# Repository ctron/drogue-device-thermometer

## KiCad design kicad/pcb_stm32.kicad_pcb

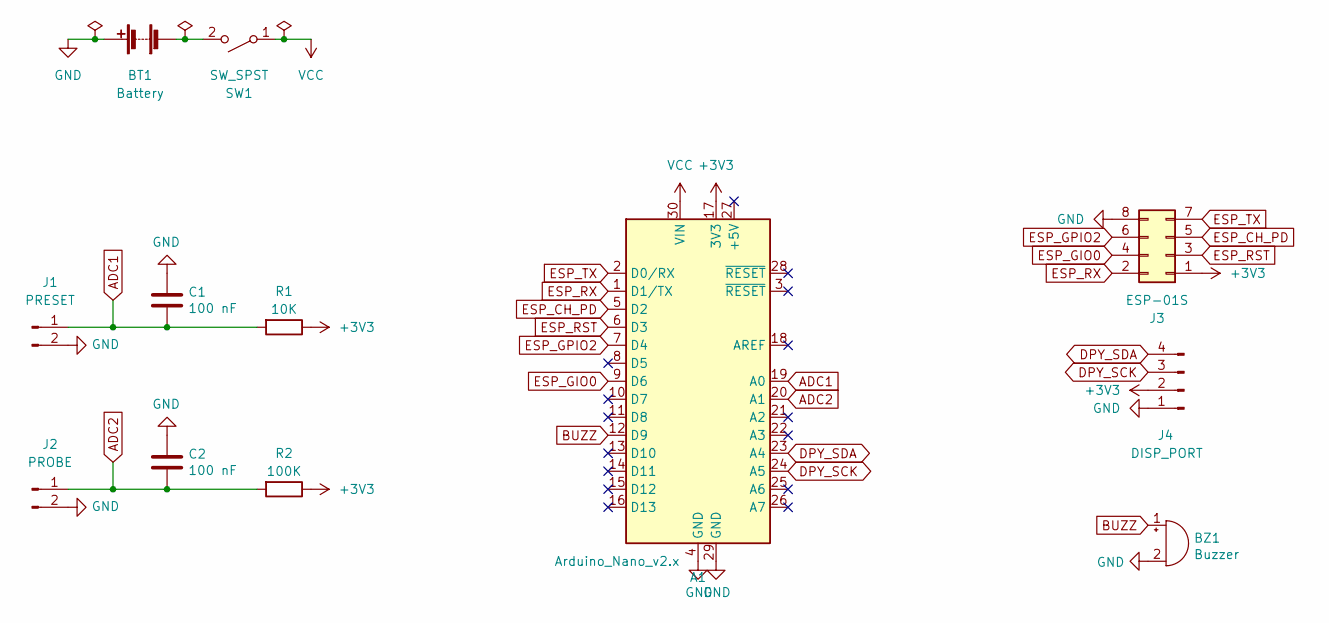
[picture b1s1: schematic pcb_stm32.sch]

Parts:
A1: Arduino_Nano_v2.x; Arduino_Nano
BT1: Battery; JST_PH_B2B-PH-K_1x02_P2.00mm_Vertical
BZ1: Buzzer; Buzzer_12x9.5RM7.6
C1, C2: 100 nF; C_0603_1608Metric
J1: PRESET; JST_PH_B2B-PH-K_1x02_P2.00mm_Vertical
J2: PROBE; JST_PH_B2B-PH-K_1x02_P2.00mm_Vertical
J3: ESP-01S; PinSocket_2x04_P2.54mm_Vertical
J4: DISP_PORT; JST_PH_B4B-PH-K_1x04_P2.00mm_Vertical
R1: 10K; R_0603_1608Metric
R2: 100K; R_0603_1608Metric
SW1: SW_SPST; JST_PH_B2B-PH-K_1x02_P2.00mm_Vertical

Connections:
+3V3: A1.17 (3V3), J3.1, J4.2, R1.1, R2.1
ADC1: A1.19 (A0), C1.2, J1.1, R1.2
ADC2: A1.20 (A1), C2.2, J2.1, R2.2
BUZZ: A1.12 (D9), BZ1.1 (-)
DPY_SCK: A1.24 (A5), J4.3
DPY_SDA: A1.23 (A4), J4.4
ESP_CH_PD: A1.5 (D2), J3.5
ESP_GIO0: A1.9 (D6), J3.4
ESP_GPIO2: A1.7 (D4), J3.6
ESP_RST: A1.6 (D3), J3.3
ESP_RX: A1.1 (D1/TX), J3.2
ESP_TX: A1.2 (D0/RX), J3.7
GND: A1.4 (GND), A1.29 (GND), BT1.1 (+), BZ1.2 (+), C1.1, C2.1, J1.2, J2.2, J3.8, J4.1
unnamed: BT1.2 (-), SW1.2 (B)
VCC: A1.30 (VIN), SW1.1 (A)

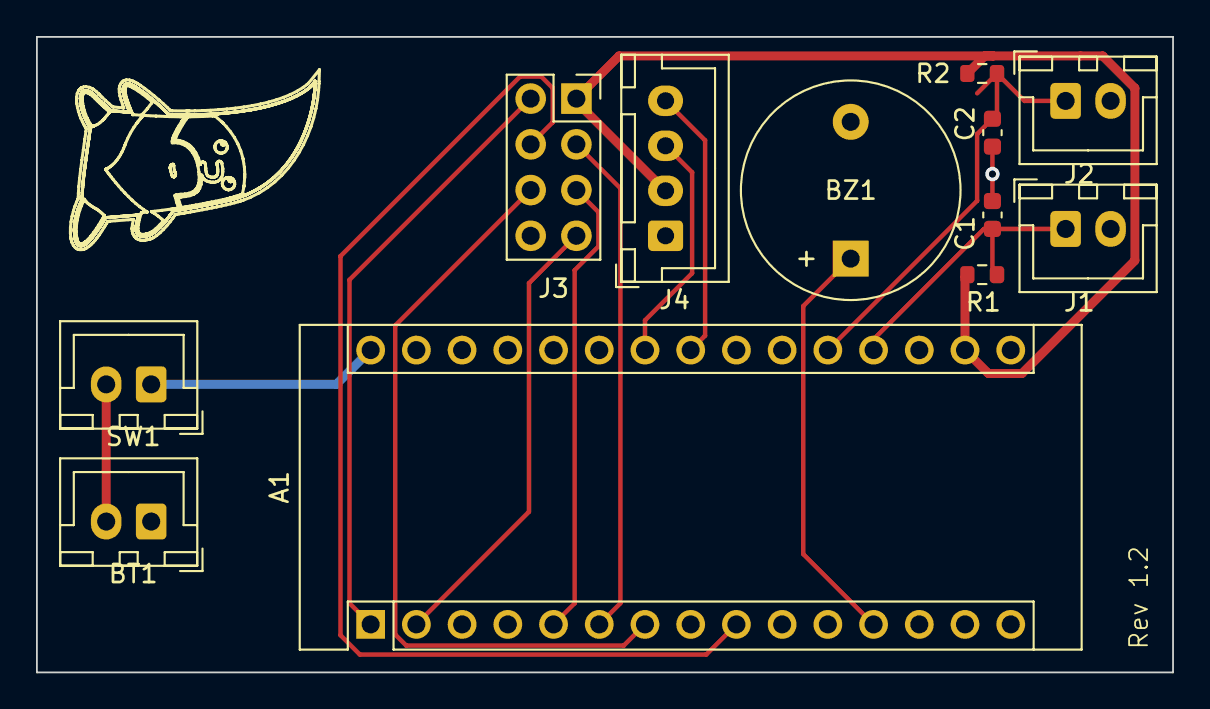
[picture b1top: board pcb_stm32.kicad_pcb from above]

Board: 2 copper layers, 63.1 x 35.3 mm, 12 parts (0 on the bottom side), 15 nets.

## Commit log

2021-06-26 initial import
2021-06-26 first stm32 based version
2021-06-26 Add second reading
2021-06-26 Add temperature conversion
2021-07-02 Compiles with display
2021-07-02 Rewire display
2021-09-27 Update to newer commits
2021-09-27 A few fixes
